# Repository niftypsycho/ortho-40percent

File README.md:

# ortho-40percent
 A 40% ortholinear mechanical keyboard with hotswaps. Designed to become familiar with keyboard fabrication and remove the need for soldering.  

# INSTRUCTIONS FOR FLASHING  
If you do not already have QMK MSYS installed do so here: https://msys.qmk.fm/  
After installing run `qmk setup`  
Clone the folder labeled mvfang located in the SOFTWARE folder and paste it into qmk_firmware/keyboards  
Test your environment by running `qmk compile -kb mvfang -km default`. This will compile the default keymap included in the mvfang folder.  
  
# EDITING AND FLASHING YOUR KEYMAP  
mvFang uses a nonstandard row-column setup than most custom keyboards. However, this has been basically abstracted away through the config.h and mvfang.h files. Unless you are absolutely certain you know what you are doing you should never interact with those files.  
  
Because this is a hotswap keyboard the option exists to use a single 2u key in the space occupied by the 5th and 6th, and 7th and 8th 1u keys respectively. The config files leave these 2u spaces active as mappable keys during all flashes.  
  
STEP 1 - Create a new keymap  
Copy the `default` keymap by running `qmk new-keymap`. Once it is created open the `keymap.c` file with any text editor. The keycodes are laid out to match the key position with the optional 2 2u keys on the last row. For a list of possible keycodes look at this doc: https://docs.qmk.fm/#/keycodes  
  
STEP 2 - Adding additional layers  
Adding layers is possible as long as you keep the same organization provided in the `LAYOUT_ALL`.  
  
STEP 3 - Flashing your custom keymap  
Make sure the keyboard is not inside the case, or that you have access to the reset button located on the bottom of the board. With the keyboard plugged into your computer double-tap the reset button. You should hear the USB connect noise (if you're on Windows) which means your board is in bootloader mode. Run `qmk flash -kb mvfang -km <my_keymap>`. If everything completes, congratulations.

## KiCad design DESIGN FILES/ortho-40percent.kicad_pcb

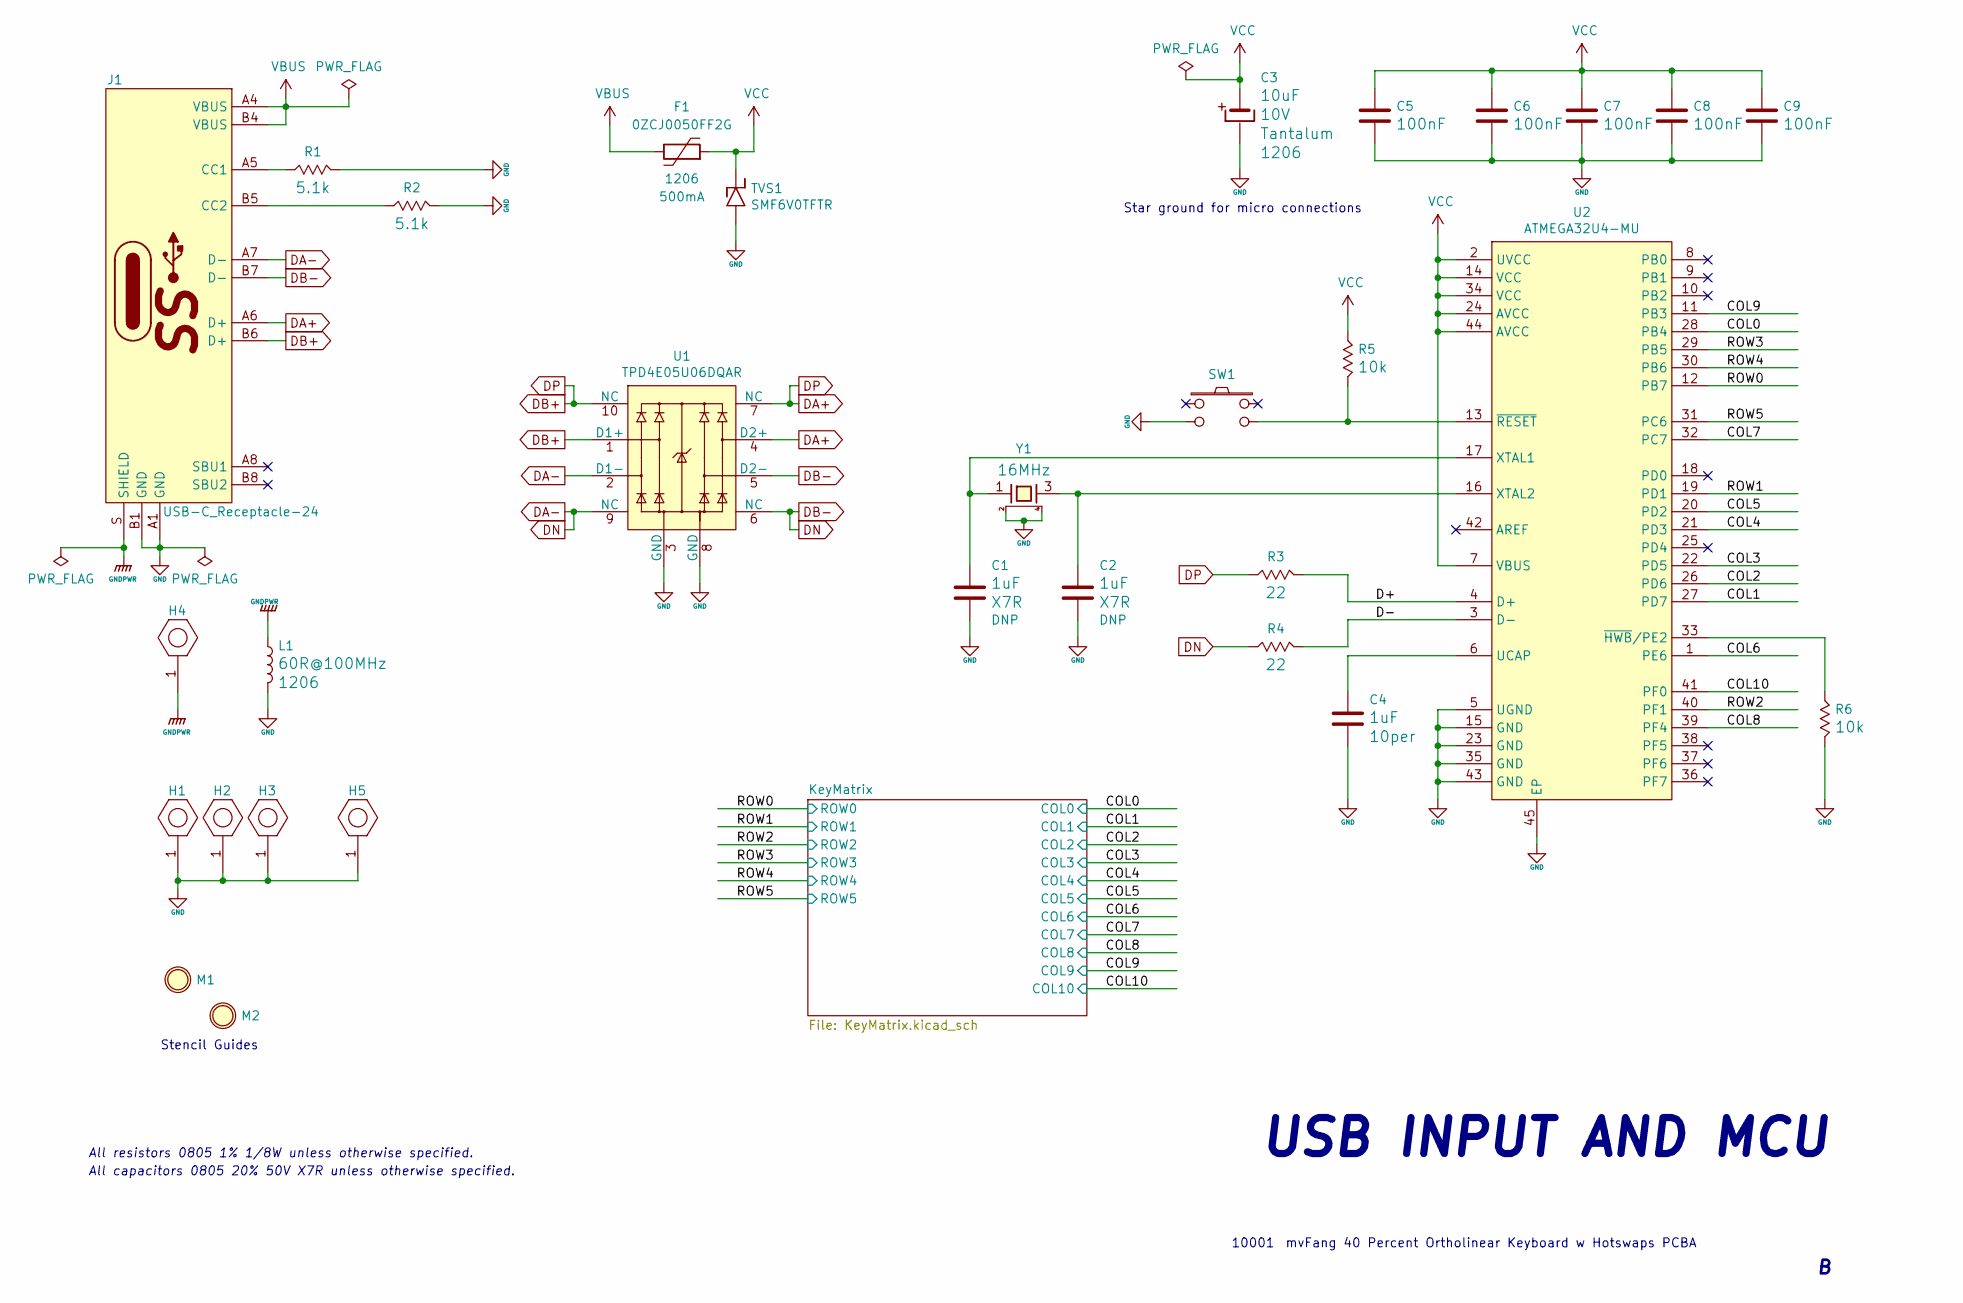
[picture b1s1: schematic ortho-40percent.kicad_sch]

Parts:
C1, C2: C; C_0805; Voltage Rating 50V; Tolerance 20per; MPN DNP
C3: CP_tantalum; CP_TANTALUM_1206; Voltage Rating 10V; Tolerance 20per; MPN T520A106M010ATE080
C4: C; C_0805; Voltage Rating 50V; Tolerance 10per; MPN CL21B105KBFNNNG
C5: C; C_0805; Voltage Rating 50V; Tolerance 20per; MPN C0805C104M5RACTU
C6, C7, C8, C9: C; C_0805; Voltage Rating 50V; Tolerance ±20%; MPN C0805C104M5RACTU
F1: F; F_1206; MPN 0ZCJ0050FF2G
H1, H2, H3, H4, H5: H_MountingHole_Screw_withPin; H_Screw-M2_Countersunk; MPN DNP
J1: USB-C_Receptacle-24; USB-C_Amphenol_12401598E4; MPN DNP
L1: L; L_1206; Current Rating 4A; Tolerance 20per; MPN FBMJ3216HM600-T
M1, M2: M_StencilGuide; STENCIL_GUIDE_HOLE; MPN DNP
R1, R2: R; R_0805; Tolerance 1per; MPN ERJ-6ENF5101V
R3, R4: R; R_0805; Tolerance 1per; MPN RC0805FR-0722RL
R5, R6: R; R_0805; Tolerance 1per; MPN RC0805FR-0710KL
SW1: SW_NO_4-Pin; SW_C+K_4-SMD-Gullwing_5.2x5.2mm_H1.6mm; MPN RS-187R05A2-DS MT RT
TVS1: TVS_Unidirectional; SOD-123F; MPN SMF6V0TFTR
U1: U_TPD4E05U06DQAR; UFDFN-10; MPN TPD4E05U06DQAR
U2: U_ATmega32u4-MU; VQFN-44-1EP_7x7mm_P0.5mm_ThermalVias; MPN ATMEGA32U4-MU
Y1: XTAL_4Lead; XTAL_4-SMD_3.2x2.5mm; MPN CX3225SB16000D0GZJC1

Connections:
/COL0: U2.28 (PB4); also elsewhere on the board
/COL1: U2.27 (PD7); also elsewhere on the board
/COL2: U2.26 (PD6); also elsewhere on the board
/COL3: U2.22 (PD5); also elsewhere on the board
/COL4: U2.21 (PD3); also elsewhere on the board
/COL5: U2.20 (PD2); also elsewhere on the board
/COL6: U2.1 (PE6); also elsewhere on the board
/COL7: U2.32 (PC7); also elsewhere on the board
/COL8: U2.39 (PF4); also elsewhere on the board
/COL9: U2.11 (PB3); also elsewhere on the board
/COL10: U2.41 (PF0); also elsewhere on the board
/D+: R3.1, U2.4 (D+)
/D-: R4.1, U2.3 (D-)
/ROW0: U2.12 (PB7); also elsewhere on the board
/ROW1: U2.19 (PD1); also elsewhere on the board
/ROW2: U2.40 (PF1); also elsewhere on the board
/ROW3: U2.29 (PB5); also elsewhere on the board
/ROW4: U2.30 (PB6); also elsewhere on the board
/ROW5: U2.31 (PC6); also elsewhere on the board
DA+: J1.A6 (D+), J1.B6 (D+), R3.2, U1.1 (D1+), U1.4 (D2+), U1.7 (NC), U1.10 (NC)
DA-: J1.A7 (D-), J1.B7 (D-), R4.2, U1.2 (D1-), U1.5 (D2-), U1.6 (NC), U1.9 (NC)
GND: C1.2, C2.2, C3.2, C4.2, C5.2, C6.2, C7.2, C8.2, C9.2, H1.1, H2.1, H3.1, H5.1, J1.A1 (GND), J1.B1 (GND), L1.2, R1.1, R2.1, R6.1, SW1.2 (in), TVS1.A, U1.3 (GND), U1.8 (GND), U2.5 (UGND), U2.15 (GND), U2.23 (GND), U2.35 (GND), U2.43 (GND), U2.45 (EP), Y1.2 (case), Y1.4 (case)
GNDPWR: H4.1, J1.S (SHIELD), L1.1
unnamed: C1.1, U2.17 (XTAL1), Y1.1
unnamed: C2.1, U2.16 (XTAL2), Y1.3
unnamed: C4.1, U2.6 (UCAP)
unnamed: J1.A5 (CC1), R1.2
unnamed: J1.B5 (CC2), R2.2
unnamed: R5.1, SW1.4 (out), U2.13 (~RESET)
unnamed: R6.2, U2.33 (~HWB/PE2)
VBUS: F1.1, J1.A4 (VBUS), J1.B4 (VBUS)
VCC: C3.1, C5.1, C6.1, C7.1, C8.1, C9.1, F1.2, R5.2, TVS1.K, U2.2 (UVCC), U2.7 (VBUS), U2.14 (VCC), U2.24 (AVCC), U2.34 (VCC), U2.44 (AVCC)

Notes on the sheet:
10001
All resistors 0805 1% 1/8W unless otherwise specified.
All capacitors 0805 20% 50V X7R unless otherwise specified.
USB INPUT AND MCU
mvFang 40 Percent Ortholinear Keyboard w Hotswaps PCBA
Star ground for micro connections
Stencil Guides

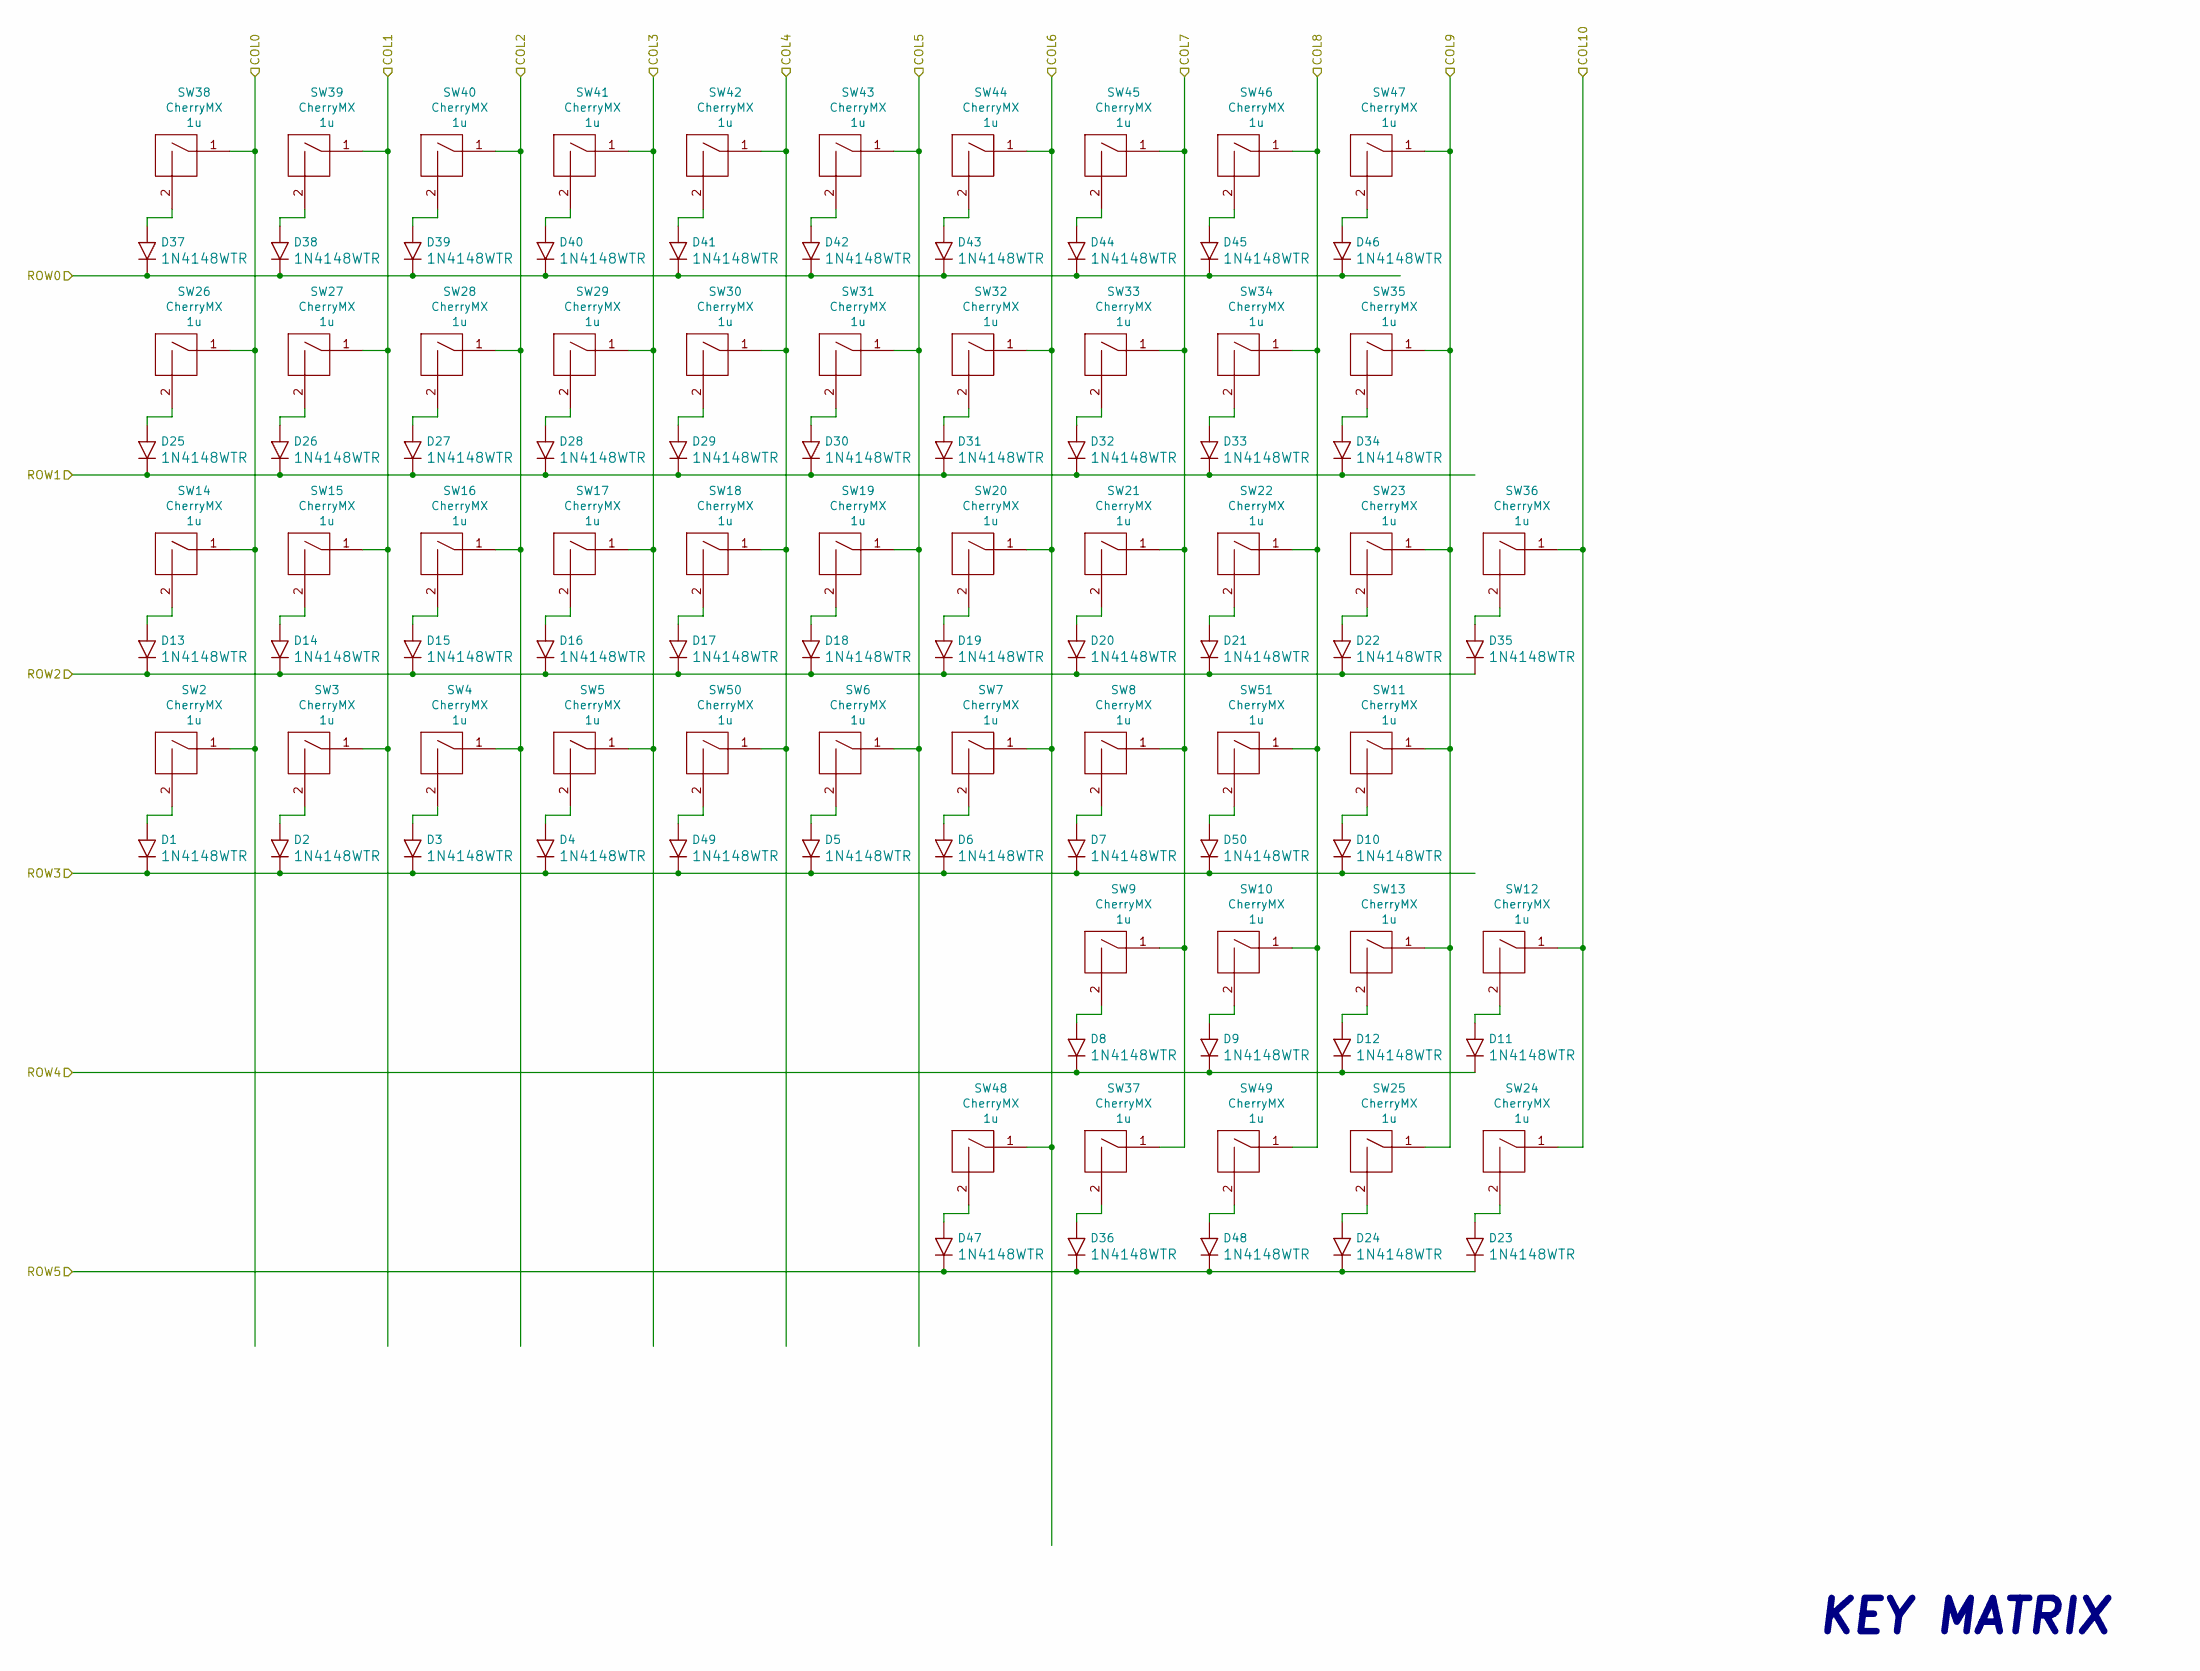
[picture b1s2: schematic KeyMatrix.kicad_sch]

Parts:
D1, D2, D3, D4, D5, D6, D7, D8, D9, D10, D11, D12, D13, D14, D15, D16, D17, D18, D19, D20, D21, D22, D23, D24, D25, D26, D27, D28, D29, D30, D31, D32, D33, D34, D35, D36, D37, D38, D39, D40, D41, D42, D43, D44, D45, D46, D47, D48, D49, D50: D; SOD-123; Voltage Rating 75V; Current Rating 250mA; MPN 1N4148WTR
SW2, SW3, SW4, SW5, SW6, SW7, SW8, SW9, SW10, SW11, SW12, SW13, SW14, SW15, SW16, SW17, SW18, SW19, SW20, SW21, SW22, SW23, SW24, SW25, SW26, SW27, SW28, SW29, SW30, SW31, SW32, SW33, SW34, SW35, SW36, SW37, SW38, SW39, SW40, SW41, SW42, SW43, SW44, SW45, SW46, SW47, SW48, SW49: CherryMX; SW_Cherry-MX_1U_PCB-Mount_Kailh-Hot-Swap; MPN DNP
SW50, SW51: CherryMX; SW_Cherry-MX_2U_PCB-Mount_Kailh-Hot-Swap; MPN DNP

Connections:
/COL0: SW2.1 (COL), SW14.1 (COL), SW26.1 (COL), SW38.1 (COL); also elsewhere on the board
/COL1: SW3.1 (COL), SW15.1 (COL), SW27.1 (COL), SW39.1 (COL); also elsewhere on the board
/COL2: SW4.1 (COL), SW16.1 (COL), SW28.1 (COL), SW40.1 (COL); also elsewhere on the board
/COL3: SW5.1 (COL), SW17.1 (COL), SW29.1 (COL), SW41.1 (COL); also elsewhere on the board
/COL4: SW18.1 (COL), SW30.1 (COL), SW42.1 (COL), SW50.1 (COL); also elsewhere on the board
/COL5: SW6.1 (COL), SW19.1 (COL), SW31.1 (COL), SW43.1 (COL); also elsewhere on the board
/COL6: SW7.1 (COL), SW20.1 (COL), SW32.1 (COL), SW44.1 (COL), SW48.1 (COL); also elsewhere on the board
/COL7: SW8.1 (COL), SW9.1 (COL), SW21.1 (COL), SW33.1 (COL), SW37.1 (COL), SW45.1 (COL); also elsewhere on the board
/COL8: SW10.1 (COL), SW22.1 (COL), SW34.1 (COL), SW46.1 (COL), SW49.1 (COL), SW51.1 (COL); also elsewhere on the board
/COL9: SW11.1 (COL), SW13.1 (COL), SW23.1 (COL), SW25.1 (COL), SW35.1 (COL), SW47.1 (COL); also elsewhere on the board
/COL10: SW12.1 (COL), SW24.1 (COL), SW36.1 (COL); also elsewhere on the board
/ROW0: D37.K, D38.K, D39.K, D40.K, D41.K, D42.K, D43.K, D44.K, D45.K, D46.K; also elsewhere on the board
/ROW1: D25.K, D26.K, D27.K, D28.K, D29.K, D30.K, D31.K, D32.K, D33.K, D34.K; also elsewhere on the board
/ROW2: D13.K, D14.K, D15.K, D16.K, D17.K, D18.K, D19.K, D20.K, D21.K, D22.K, D35.K; also elsewhere on the board
/ROW3: D1.K, D2.K, D3.K, D4.K, D5.K, D6.K, D7.K, D10.K, D49.K, D50.K; also elsewhere on the board
/ROW4: D8.K, D9.K, D11.K, D12.K; also elsewhere on the board
/ROW5: D23.K, D24.K, D36.K, D47.K, D48.K; also elsewhere on the board
unnamed: D1.A, SW2.2 (ROW)
unnamed: D2.A, SW3.2 (ROW)
unnamed: D3.A, SW4.2 (ROW)
unnamed: D4.A, SW5.2 (ROW)
unnamed: D5.A, SW6.2 (ROW)
unnamed: D6.A, SW7.2 (ROW)
unnamed: D7.A, SW8.2 (ROW)
unnamed: D8.A, SW9.2 (ROW)
unnamed: D9.A, SW10.2 (ROW)
unnamed: D10.A, SW11.2 (ROW)
unnamed: D11.A, SW12.2 (ROW)
unnamed: D12.A, SW13.2 (ROW)
unnamed: D13.A, SW14.2 (ROW)
unnamed: D14.A, SW15.2 (ROW)
unnamed: D15.A, SW16.2 (ROW)
unnamed: D16.A, SW17.2 (ROW)
unnamed: D17.A, SW18.2 (ROW)
unnamed: D18.A, SW19.2 (ROW)
unnamed: D19.A, SW20.2 (ROW)
unnamed: D20.A, SW21.2 (ROW)
unnamed: D21.A, SW22.2 (ROW)
unnamed: D22.A, SW23.2 (ROW)
unnamed: D23.A, SW24.2 (ROW)
unnamed: D24.A, SW25.2 (ROW)
unnamed: D25.A, SW26.2 (ROW)
unnamed: D26.A, SW27.2 (ROW)
unnamed: D27.A, SW28.2 (ROW)
unnamed: D28.A, SW29.2 (ROW)
unnamed: D29.A, SW30.2 (ROW)
unnamed: D30.A, SW31.2 (ROW)
unnamed: D31.A, SW32.2 (ROW)
unnamed: D32.A, SW33.2 (ROW)
unnamed: D33.A, SW34.2 (ROW)
unnamed: D34.A, SW35.2 (ROW)
unnamed: D35.A, SW36.2 (ROW)
unnamed: D36.A, SW37.2 (ROW)
unnamed: D37.A, SW38.2 (ROW)
unnamed: D38.A, SW39.2 (ROW)
unnamed: D39.A, SW40.2 (ROW)
unnamed: D40.A, SW41.2 (ROW)
unnamed: D41.A, SW42.2 (ROW)
unnamed: D42.A, SW43.2 (ROW)
unnamed: D43.A, SW44.2 (ROW)
unnamed: D44.A, SW45.2 (ROW)
unnamed: D45.A, SW46.2 (ROW)
unnamed: D46.A, SW47.2 (ROW)
unnamed: D47.A, SW48.2 (ROW)
unnamed: D48.A, SW49.2 (ROW)
unnamed: D49.A, SW50.2 (ROW)
unnamed: D50.A, SW51.2 (ROW)

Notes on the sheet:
KEY MATRIX

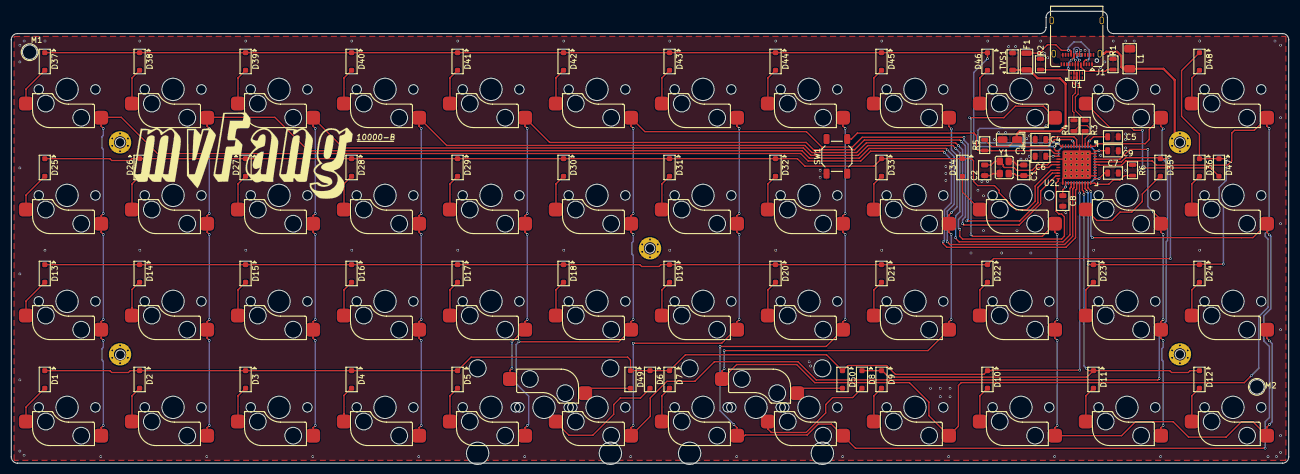
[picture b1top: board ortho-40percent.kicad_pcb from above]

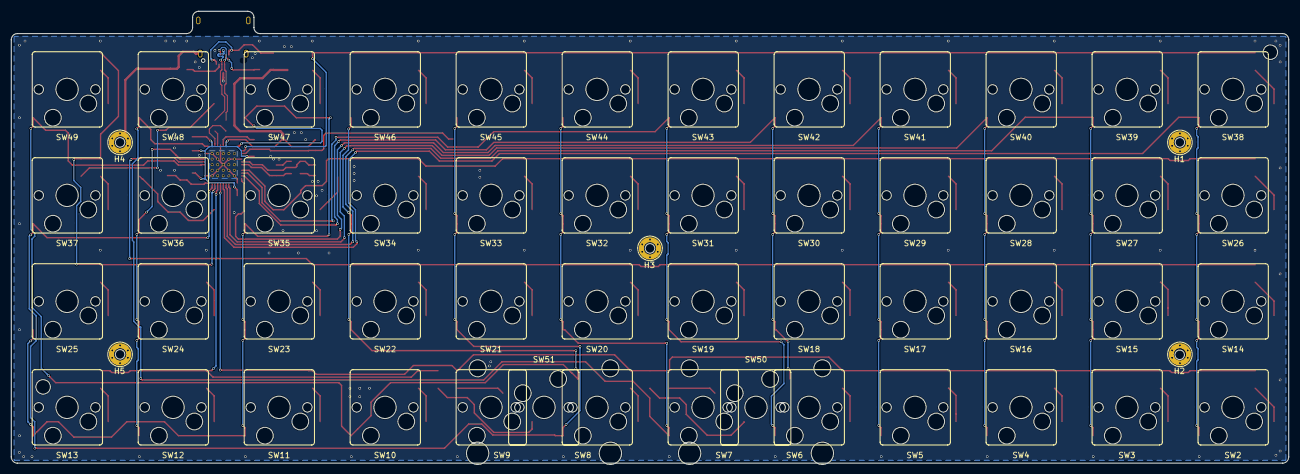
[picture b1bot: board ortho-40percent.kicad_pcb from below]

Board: 2 copper layers, 229.0 x 81.0 mm, 130 parts (55 on the bottom side), 82 nets.

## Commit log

2020-07-23 Initialize Project
    Created KiCad project.
2020-07-24 Footprint library creation
    Began creation of mx 1u footprint
2020-07-26 Switch footprint completion
    Completed cherry mx switch footprints - Plate mount, pcb mount, and kailh hot swap swich variants
2020-07-30 Footprint creation
    Created ortho-40percent footprint library. Created footprints for 1206 fuse, usb-c tvs, and 1206 inductor. Modified SOD-123F from different library. Created USB-C footprint.
2020-09-26 Created KeyMatrix schematic
    Added new footprints and associated 3d models. Created KeyMatrix schematic sheet.
2020-09-26 Clarified Keycaps
    Added drawing outline of DSA keycap dimension. Added DSA keycap 3d model to 1u mx pcbmount switch. Placed two rows of switches on pcb layout.
2020-10-07 PCB Key Layout
    Locked placement of main key matrix on pcb, began placement of matrix diodes.
2021-03-05 Case outline and mounting
    Received kprepublic case, used dimensions to set drawing of case and pcb outline. Created M2 screw footprint and added mounting holes to project. Tied screws to power gnd, will possibly change to sig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
2021-03-05 Changed name of old library
    Library was using incorrect name left over from unrelated project.
2021-03-08 ESD overhaul and mechanical finish
    Finished mounting hole placement with respect to case dimensions. Rotated all switches 180 to allow for placement of USB-C connector. Redid ground connections to have connector shield grounded to cas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
2021-03-13 2u footprint and plate comments
    Finished 2u footprint in all styles. Added cutouts by using Cmts.User layer.
2021-03-16 Fixed case, pcb, screw locations
    Set origin to hole on bottom-left switch, based all pcb and case dimensions on that hole. Relocated screws to new locations, now they are symmetrical with key positions.
2021-04-14 Micro change and origin reset
    Returned origin to center hole of bottom-left switch instead of pin 1 hole.
    Added 3mm ground trace margin and mtg hole margin.
    Created 44-VQFN footprint and schematic symbol, and updated micro to new part.
2021-04-28 USB connector update
    Added connector keepout zone and PCB edge text for usb-c connector footprint. Attempted routing and movement of D+/D- lines.
2021-04-30 Routing
    more routing and placement
2021-04-30 USB connections
    Completed USB-C routing, tested ground planes and settings for robustness
2021-05-02 Beginning switch routing
    Finished routing of all micro, usb, and power components. Beginning placement and routing of diodes and keyswitches.
2021-05-03 More key routing
    Remapped keys to rows/columns to help optimize. Routed more.
2021-05-04 More routing
    more routing
2021-05-18 More routing
    even more routing
2021-07-11 Routing Finished
    All connections routed. Focusing on cleaning up for length optimization and minimal bottom plane cutting.
2021-07-12 Electrical Finished
    All electrical completed, refdes placed. Beginning to place silkscreen logos and other branding items.
2021-07-17 Hardware Complete
    Electrical completed and DRC passed.
    Silkscreen logos and info added.
    Ready for first prototype ordering.
2021-07-18 Mounting hole modifications
    Drilled holes for mounting holes were smaller than 0.3mm which many boardhouses charge extra for. Increased hole size to 0.33mm.
2022-02-24 Created and modified fabrication
    Created more sensical fabrication and assembly outputs. Differentiated between first revision and subsequent revisions.
2022-03-19 Consolidating design files
    Added directory to store design separate from production files
2022-03-19 Testing readme
2022-04-04 Added stencil guide holes
    Added 2.6mm dia guide holes at 10mm spacings to board to help with stencil alignment
2022-04-18 Fixed diode legibility
    Issue affected D26 and D27 and is fixed
2022-04-18 Added custom MV PNs to each component
    Added unique MV PN for each unique component, referenced in personal component database.
2022-06-02 Created software folder
    Added software with default keymap
2022-06-14 Added .gitignore
    Stops tracking backups and auto generated KiCad files
